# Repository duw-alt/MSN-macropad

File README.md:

# MSN-macropad
MSN shaped macropad!!

### Inspiration

I wanted to create a macropad that had a fun shape to sit at my desk. I created a macropad using 3 switches, 1 rp2040, 1 OLED and 1 rotary encoder. 

### Challenges

This was super challenging for me since it was my first time designing a schematic, pcb and a case. I stuggled a lot but it's DONE

### Specifications

BOM: 
- 3x Cherry MX Switches
- 3x Blank DSA Keycaps
- 1x XIAO RP2040
- 2x M3x16 Bolt
- 2x M3 Heatset
- 1x 0.91" 128x32 OLED Display
- 1x EC11 Rotary Encoder
- 1x Case (2 printed parts)

Schematic            |  PCB         |   Case
:-------------------------:|:-------------------------:|:-------------------------:|
    |    |

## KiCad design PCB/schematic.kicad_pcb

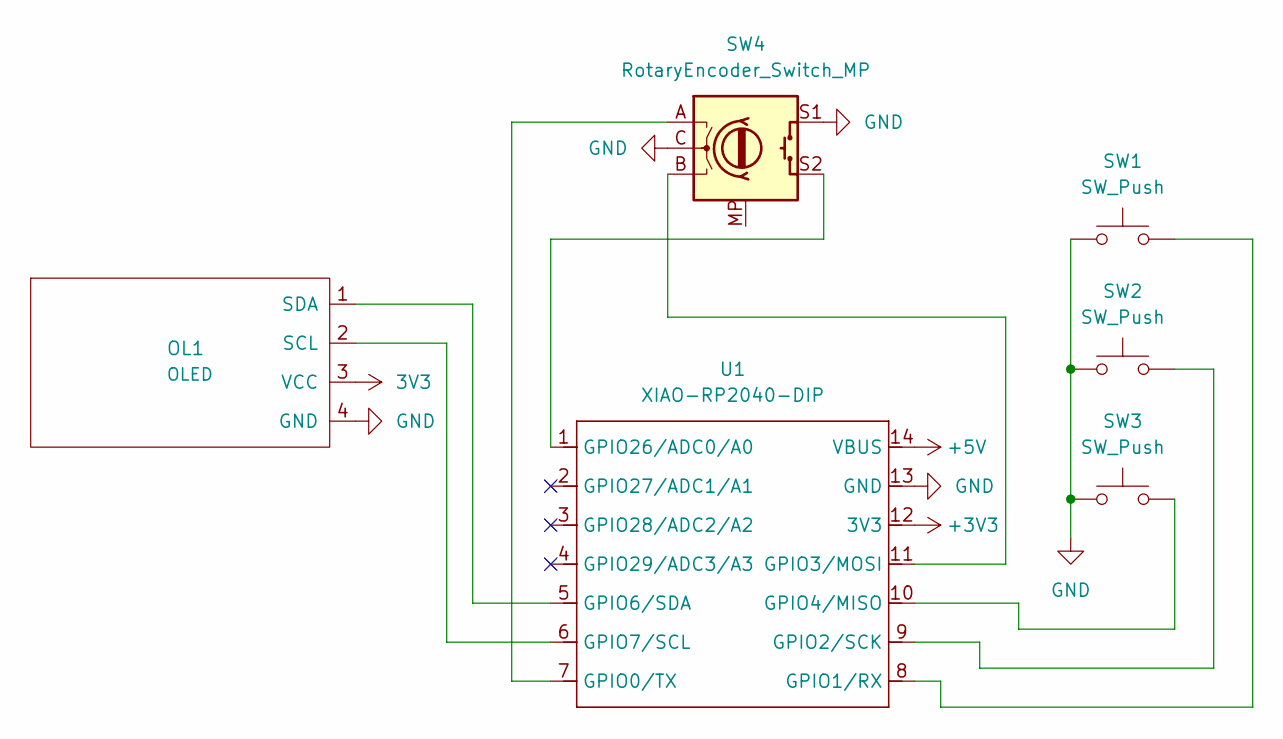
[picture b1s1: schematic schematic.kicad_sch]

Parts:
OL1: OLED; SSD1306-0.91-OLED-4pin-128x32
SW1, SW2, SW3: SW_Push; SW_Cherry_MX_1.00u_PCB
SW4: RotaryEncoder_Switch_MP; RotaryEncoder_Alps_EC11E-Switch_Vertical_H20mm
U1: XIAO-RP2040-DIP

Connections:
3V3: OL1.3 (VCC)
+3V3: U1.12 (3V3)
+5V: U1.14 (VBUS)
GND: OL1.4 (GND), SW1.1, SW2.1, SW3.1, SW4.C, SW4.S1, U1.13 (GND)
unnamed: OL1.2 (SCL), U1.6 (GPIO7/SCL)
unnamed: OL1.1 (SDA), U1.5 (GPIO6/SDA)
unnamed: SW4.A, U1.7 (GPIO0/TX)
unnamed: SW1.2, U1.8 (GPIO1/RX)
unnamed: SW2.2, U1.9 (GPIO2/SCK)
unnamed: SW4.B, U1.11 (GPIO3/MOSI)
unnamed: SW3.2, U1.10 (GPIO4/MISO)
unnamed: SW4.S2, U1.1 (GPIO26/ADC0/A0)

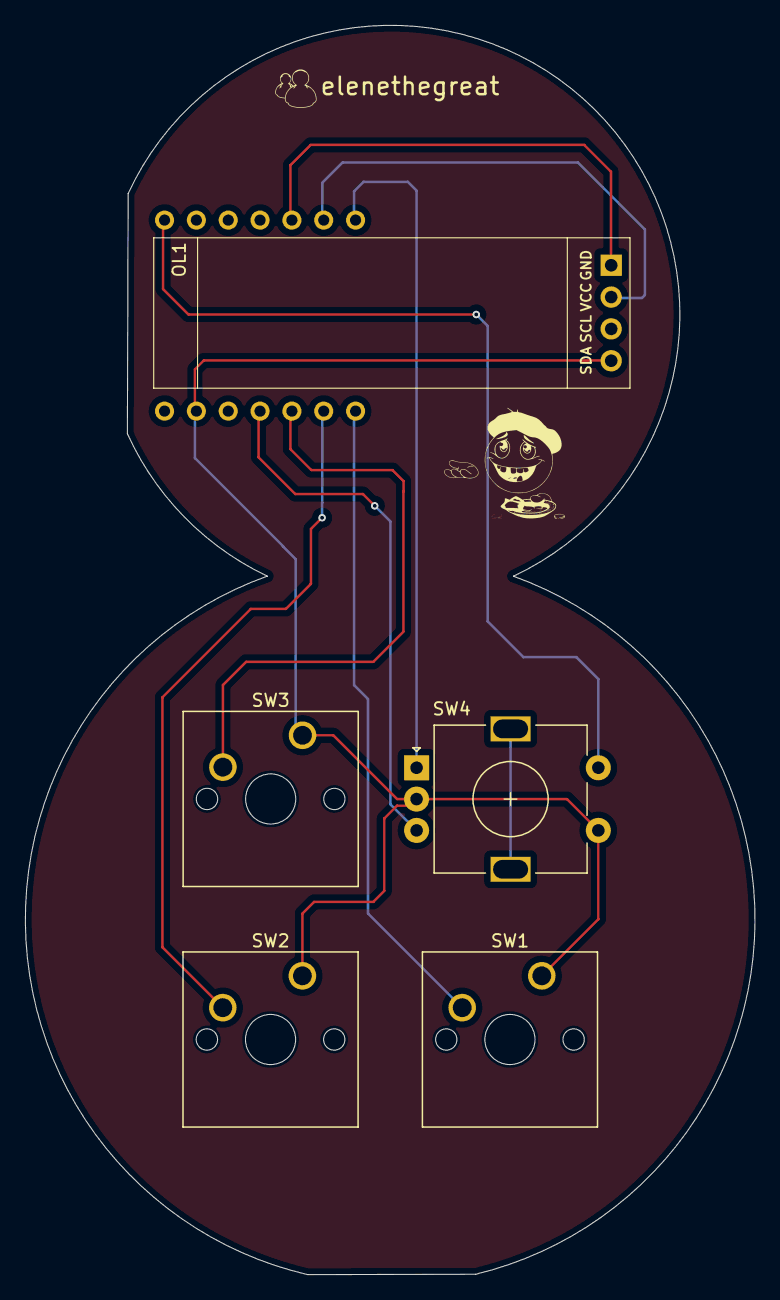
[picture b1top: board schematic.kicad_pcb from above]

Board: 2 copper layers, 58.2 x 99.7 mm, 6 parts (1 on the bottom side), 9 nets.

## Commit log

2025-12-29 added concept photos
2025-12-29 Enhance README with detailed project information
    Added sections for inspiration, challenges, and specifications.
2025-12-29 added production files
2026-01-02 Update CAD files, assets, and production files
